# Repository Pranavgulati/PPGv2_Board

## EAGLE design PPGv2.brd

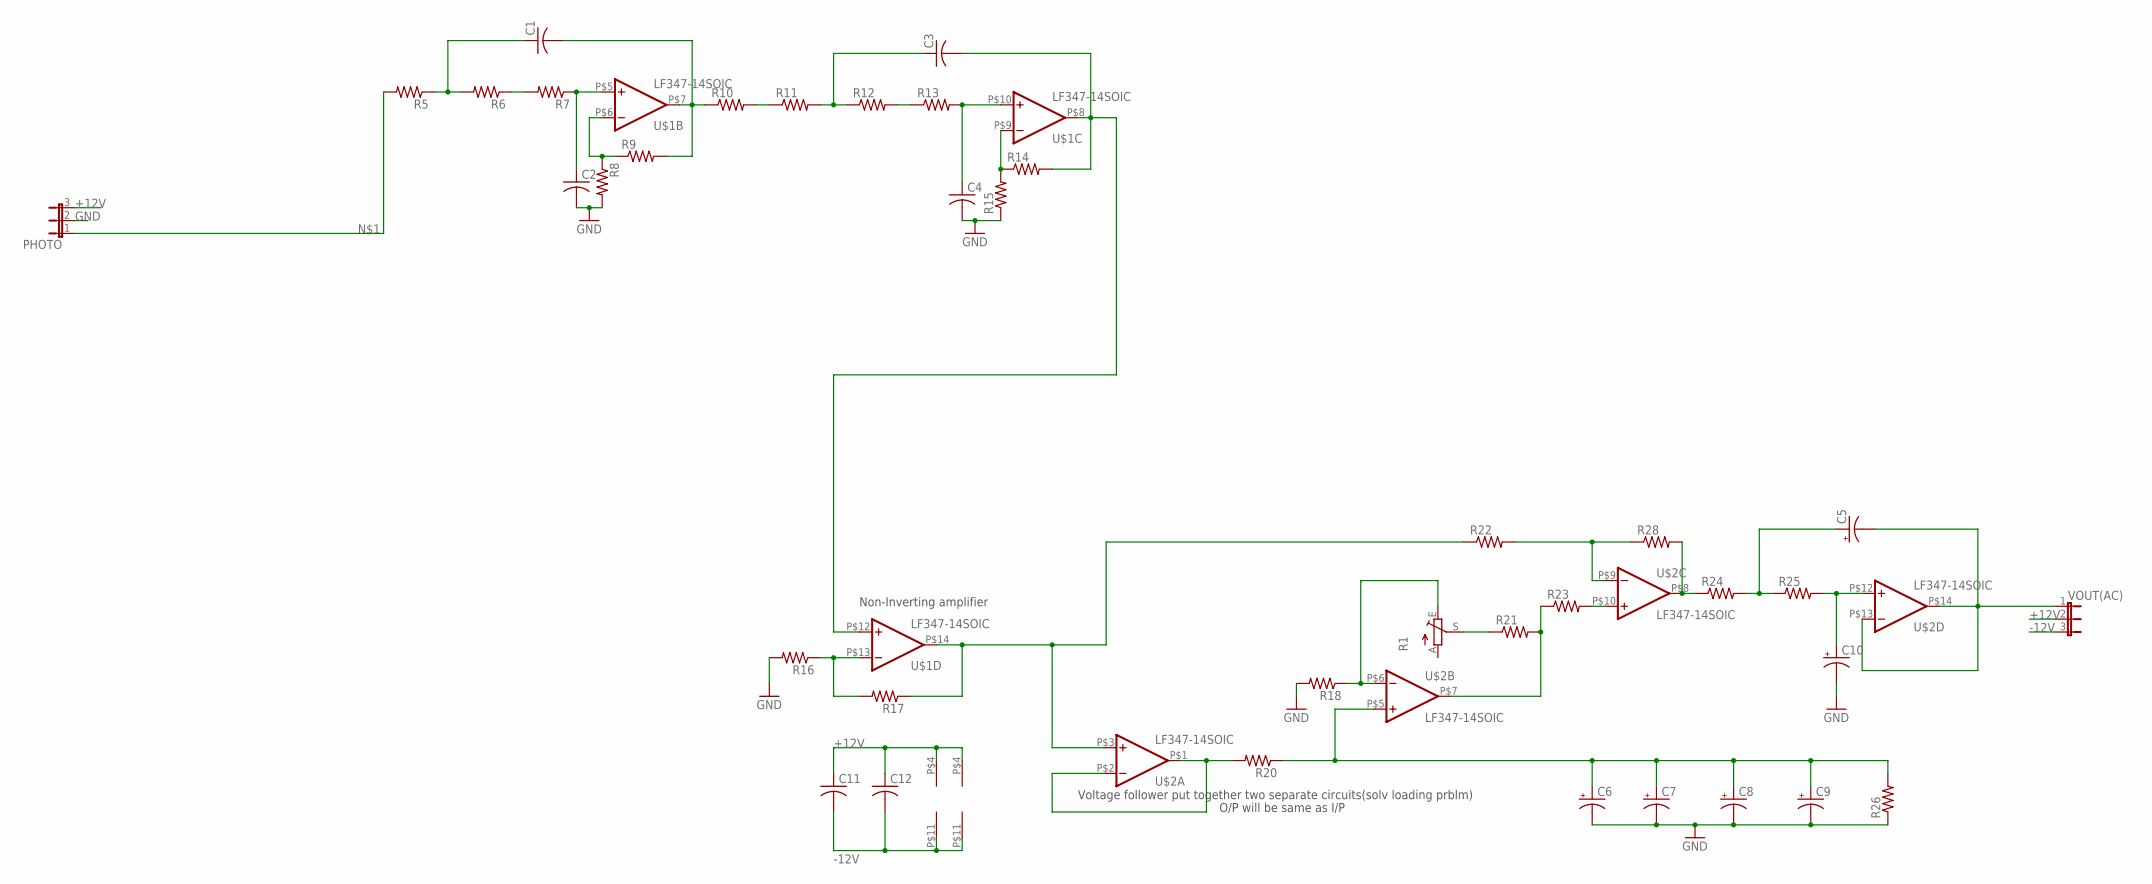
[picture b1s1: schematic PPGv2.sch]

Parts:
C1, C2, C3, C4, C11, C12: CAP0603; C0603
C5, C6, C7, C8, C9, C10: CAP_POL_10V; C/6032-28R
PHOTO: JP2E; JP2
R1: TRIM_EU-RJ9W; RJ9W
R5, R6, R7, R8, R9, R10, R11, R12, R13, R14, R15, R16, R17, R18, R20, R21, R22, R23, R24, R25, R26, R28: R-US_R0603; R0603
U$1, U$2: LF347-14SOIC; SOIC14
VOUT(AC): JP2E; JP2

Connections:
+12V: C11.1, C12.1, PHOTO.3, U$1.P$4 (VCC), U$2.P$4 (VCC), VOUT(AC).2
-12V: C11.2, C12.2, U$1.P$11 (VEE), U$2.P$11 (VEE), VOUT(AC).3
GND: C2.2, C4.2, C6.-, C7.-, C8.-, C9.-, C10.-, PHOTO.2, R8.2, R15.1, R16.2, R18.2, R26.1
unnamed: PHOTO.1, R5.2
unnamed: R8.1, R9.1, U$1.P$6 (IN-)
unnamed: C1.1, R5.1, R6.2
unnamed: R6.1, R7.2
unnamed: C2.1, R7.1, U$1.P$5 (IN+)
unnamed: C4.1, R13.2, U$1.P$10 (IN+)
unnamed: C1.2, R9.2, R10.1, U$1.P$7 (OUT)
unnamed: R10.2, R11.1
unnamed: C3.1, R11.2, R12.1
unnamed: R12.2, R13.1
unnamed: R14.1, R15.2, U$1.P$9 (IN-)
unnamed: R22.2, R28.1, U$2.P$9 (IN-)
unnamed: C3.2, R14.2, U$1.P$8 (OUT), U$1.P$12 (IN+)
unnamed: R16.1, R17.2, U$1.P$13 (IN-)
unnamed: C5.-, U$2.P$13 (IN-), U$2.P$14 (OUT), VOUT(AC).1
unnamed: R24.1, R28.2, U$2.P$8 (OUT)
unnamed: R17.1, R22.1, U$1.P$14 (OUT), U$2.P$3 (IN+)
unnamed: R23.2, U$2.P$10 (IN+)
unnamed: R21.2, R23.1, U$2.P$7 (OUT)
unnamed: R1.S, R21.1
unnamed: R1.E, R18.1, U$2.P$6 (IN-)
unnamed: R20.2, U$2.P$1 (OUT), U$2.P$2 (IN-)
unnamed: C6.+, C7.+, C8.+, C9.+, R20.1, R26.2, U$2.P$5 (IN+)
unnamed: C5.+, R24.2, R25.1
unnamed: C10.+, R25.2, U$2.P$12 (IN+)

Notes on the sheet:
Voltage follower put together two separate circuits(solv loading prblm)
O/P will be same as I/P
Non-Inverting amplifier

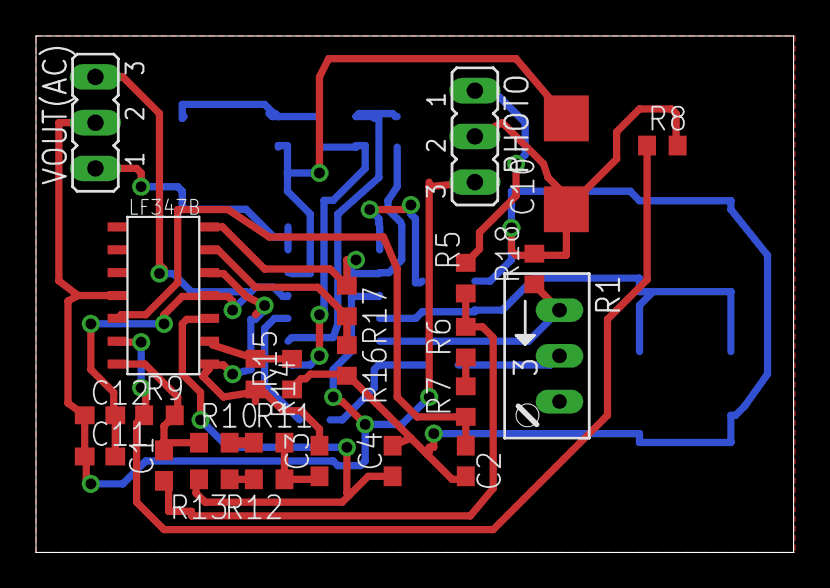
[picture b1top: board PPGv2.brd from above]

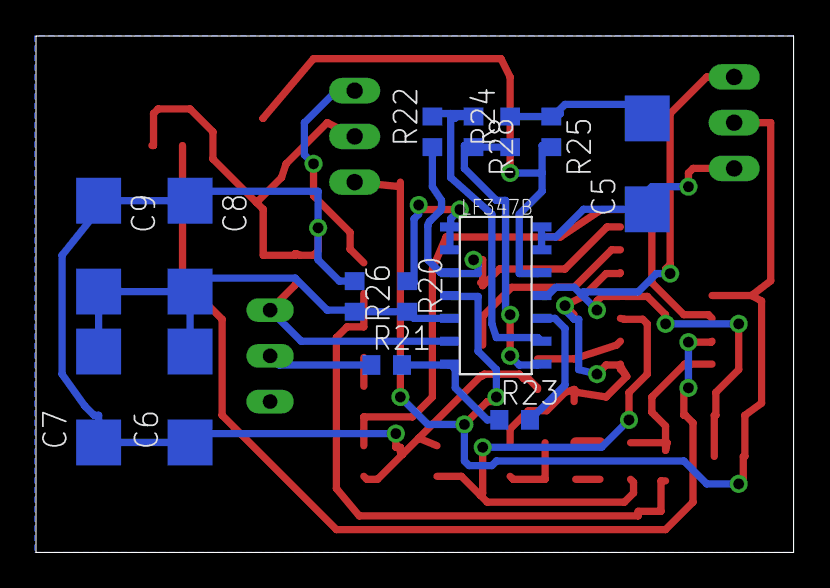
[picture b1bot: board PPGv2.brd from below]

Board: 2 copper layers, 42.1 x 28.7 mm, 39 parts (14 on the bottom side), 28 nets.

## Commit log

2016-03-04 :tada: Added .gitattributes & .gitignore files
2016-03-04 Initial
    - Previously developed board and schematic
2016-03-04 Final
    -made 2 layers each with one IC
    -final dimensions are 46.15 x 35.8 mm acc to OSHpark guidelines
2016-03-20 Before removing the extra Pins
2016-03-22 Final
    -removed extra connectors
    -without IR-INP input
2016-06-01 -final
2016-06-10 -minor changes
2016-07-30 -final iteration
